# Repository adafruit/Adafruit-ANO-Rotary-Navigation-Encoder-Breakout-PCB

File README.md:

## Adafruit ANO Rotary Navigation Encoder Breakout PCB

<a href="http://www.adafruit.com/products/5221"><br/>
Click here to purchase one from the Adafruit shop</a>

PCB files for the Adafruit ANO Rotary Navigation Encoder Breakout. 

Format is EagleCAD schematic and board layout
* https://www.adafruit.com/product/5221

### Description

The ANO rotary encoder wheel is a funky user interface element is reminiscent of the original clicking scroll wheel interface on the first  iPods. It's a nifty kit, but the pin-out is a little odd, so we made a handy breakout board that converts the funky pin set into a straight forward, breadboard-friendly header strip.

There's no pull-up or pull-down resistors on this PCB, and of course you'll need to solder the encoder onto the breakout. Then use your microcontroller's button and rotary encoder library/hardware support to interface with the pins.

You'll need 7 GPIO total: 5 buttons and 2 rotary encoder pins. There's also two COMmon pins, which you can set to ground or VCC - usually ground so that you can use the microcontroller internal pull-ups for the button/encoders. Note to make our wiring simple, our example code uses GPIO to the COM's and then sets then to outputs, but you can just wire them directly.

### License

Adafruit invests time and resources providing this open source design, please support Adafruit and open-source hardware by purchasing products from [Adafruit](https://www.adafruit.com)!

Designed by Limor Fried/Ladyada for Adafruit Industries.

Creative Commons Attribution/Share-Alike, all text above must be included in any redistribution. 
See license.txt for additional details.

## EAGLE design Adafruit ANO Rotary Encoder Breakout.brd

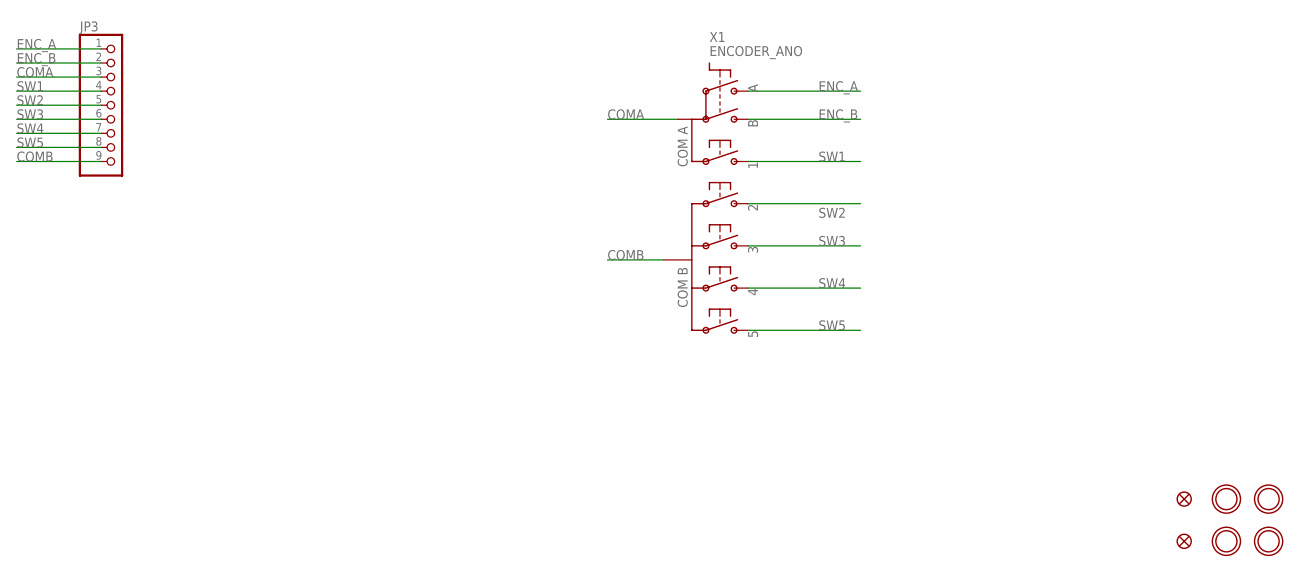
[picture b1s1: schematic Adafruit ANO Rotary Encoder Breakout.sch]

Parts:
FID3, FID4: FIDUCIAL_1MM
JP3: HEADER-1X970MIL; 1X09_ROUND_70
U$25, U$27, U$29, U$30: MOUNTINGHOLE2.5; MOUNTINGHOLE_2.5_PLATED
X1: ENCODER_ANO

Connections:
COMA: JP3.3, X1.COM_A (COMA)
COMB: JP3.9, X1.COM_B
ENC_A: JP3.1, X1.A
ENC_B: JP3.2, X1.B
SW1: JP3.4, X1.S1 (1)
SW2: JP3.5, X1.S2
SW3: JP3.6, X1.S3
SW4: JP3.7, X1.S4
SW5: JP3.8, X1.S5

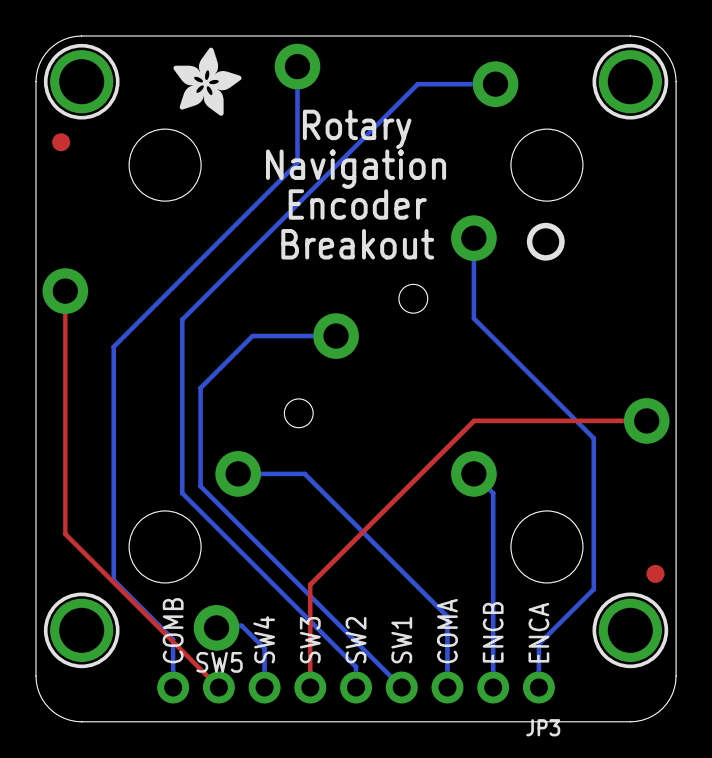
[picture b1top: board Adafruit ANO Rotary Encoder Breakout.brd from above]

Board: 2 copper layers, 35.6 x 38.1 mm, 10 parts (1 on the bottom side), 9 nets.

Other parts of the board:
U$32: ADAFRUIT_3.5MM
U$33: PCBFEAT-REV-040

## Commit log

2021-10-01 Adding board files.

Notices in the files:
parts and their libraries:
microbuilder: This work is placed in the public domain, and may be freely used for commercial and non-commercial work with the following conditions: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
